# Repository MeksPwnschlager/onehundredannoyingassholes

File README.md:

# onehundredannoyingassholes 

Piezo Buzzer Throwies which buzz every 15-30 minutes and should last months.

## Ingredients

 - ATTiny25 - 20SU
 - PCB (`kicad/`)
 - Piezo Buzzer
 - CRC2032 Battery
 - SMD CR2032 Battery Hodler
 - Code (`arduino/`)
 - SMD Solder Paste

1-1.50€/Piece

depending on what deals you get on the components.

## Making your own

### 1. Search for and buy the needed components at the electronics merchant of your choice.

For big orders `aliexpress.com` might be one of the cheaper options

### 2. Order the PCBs

We used `seeedstudio.com`, but `dirtypcbs.com` is also a cheap alternative. Maybe even buy a solder stencil to make your life easier!

### 3. Flash the chips

Use the included arduino code to flash the ATTiny25 using a POMONA Clip or other means of electrical contact and an AVR programmer.

### 4. Solder, Solder, Solder

Solder the SMD and normal compontents onto the board.

### 5. Annoy

Place the battery in the battery holder (duh) and listen to them beep!

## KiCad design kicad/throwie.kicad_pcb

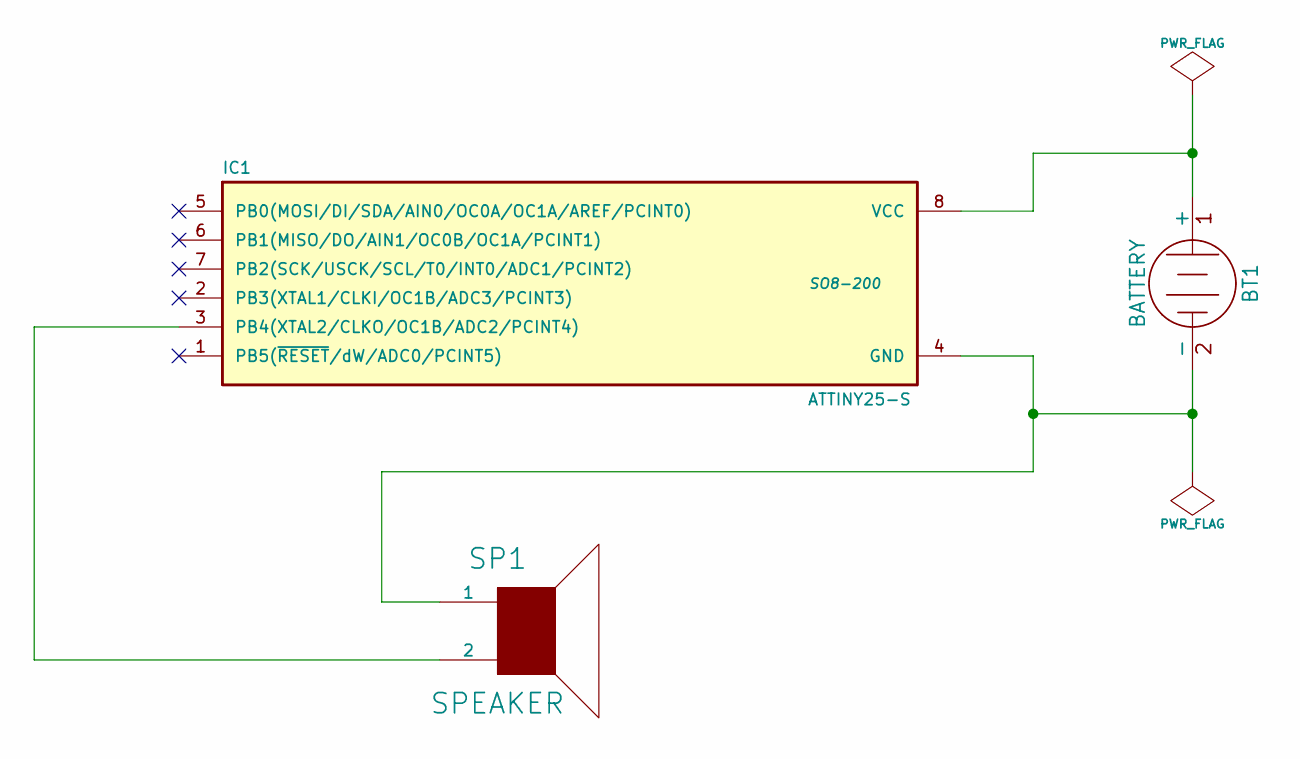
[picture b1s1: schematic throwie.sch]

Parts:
BT1: BATTERY
IC1: ATTINY25-S; SO8-200
SP1: SPEAKER

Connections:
unnamed: IC1.3 (PB4(XTAL2/CLKO/OC1B/ADC2/PCINT4)), SP1.2
unnamed: BT1.2 (-), IC1.4 (GND), SP1.1
unnamed: BT1.1 (+), IC1.8 (VCC)

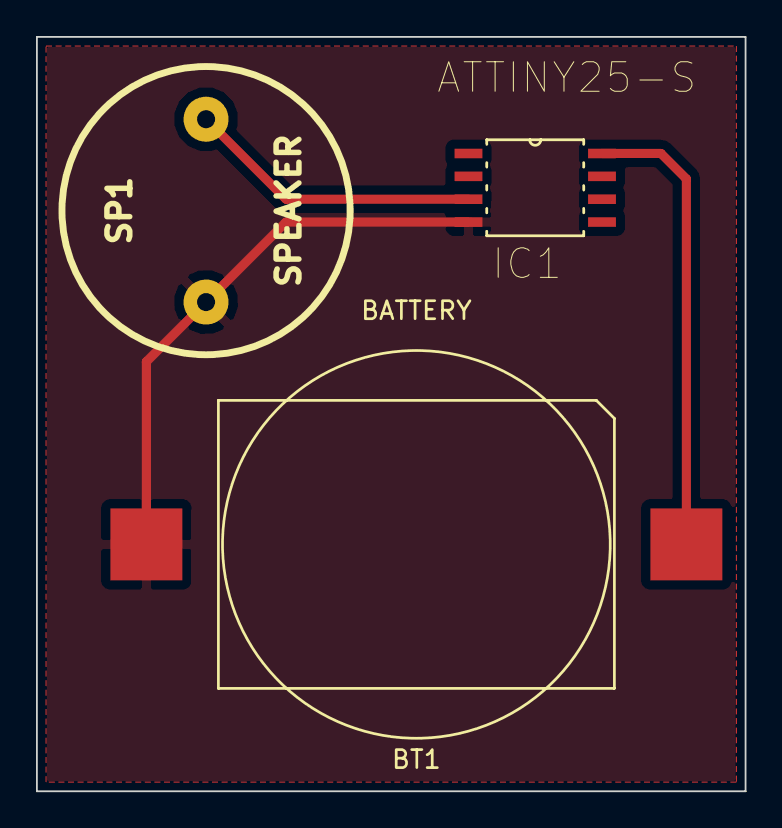
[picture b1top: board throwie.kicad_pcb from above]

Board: 2 copper layers, 39.4 x 41.9 mm, 3 parts (0 on the bottom side), 3 nets.

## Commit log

2018-02-28 update writeup
2018-06-04 update story
2018-06-04 smalify gif
2018-06-04 uodate txt
2018-06-04 update txt
